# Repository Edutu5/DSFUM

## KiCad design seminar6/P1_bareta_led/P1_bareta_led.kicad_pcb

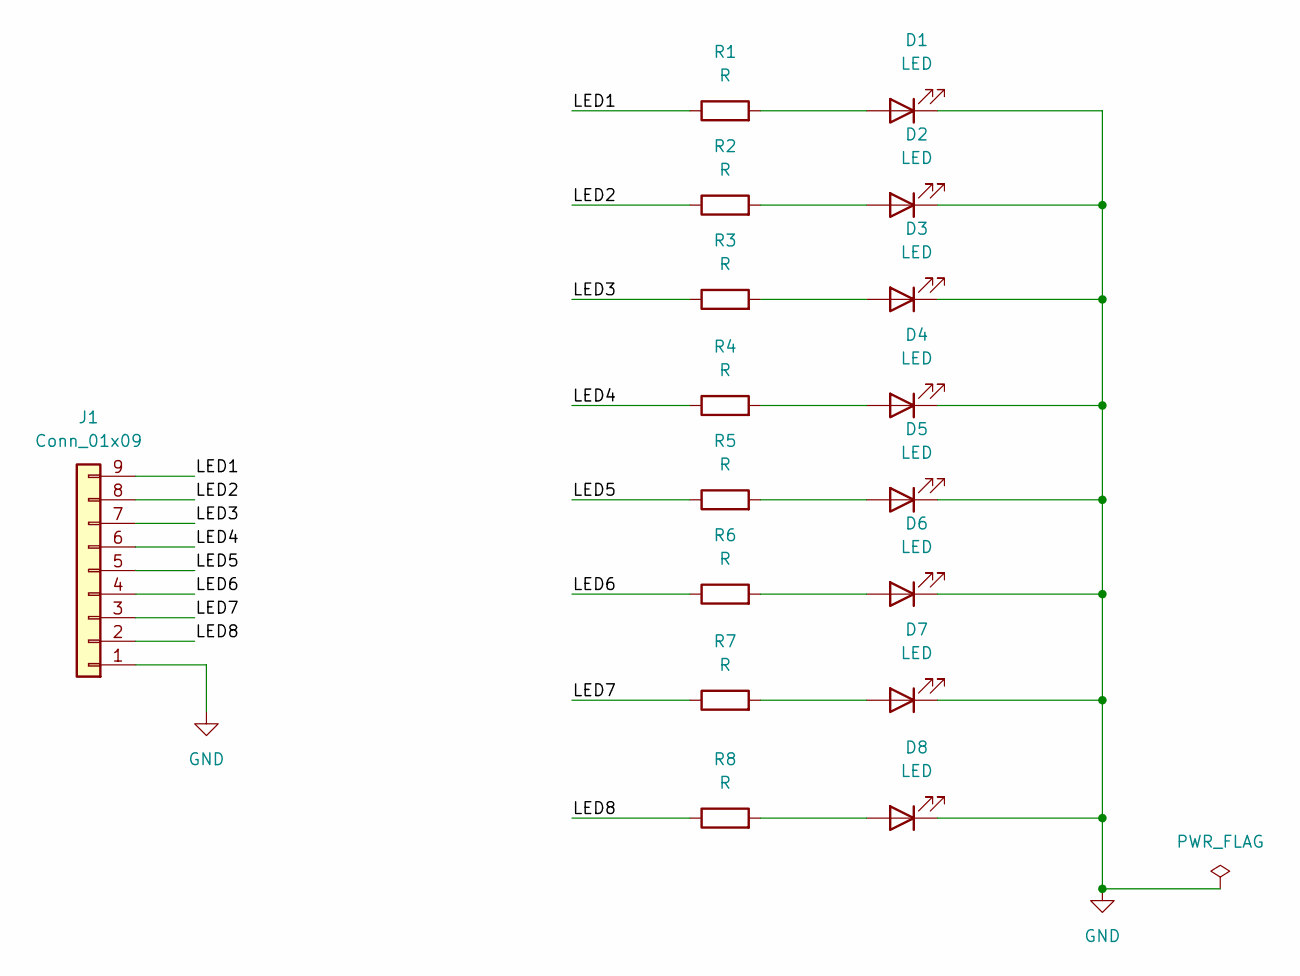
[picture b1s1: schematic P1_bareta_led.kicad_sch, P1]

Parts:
D1, D2, D3, D4, D5, D6, D7, D8: LED; LED_D5.0mm
J1: Conn_01x09
R1, R2, R3, R4, R5, R6, R7, R8: R; R_Axial_DIN0207_L6.3mm_D2.5mm_P10.16mm_Horizontal

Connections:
/LED1: J1.9, R1.1
/LED2: J1.8, R2.1
/LED3: J1.7, R3.1
/LED4: J1.6, R4.1
/LED5: J1.5, R5.1
/LED6: J1.4, R6.1
/LED7: J1.3, R7.1
/LED8: J1.2, R8.1
GND: D1.1 (K), D2.1 (K), D3.1 (K), D4.1 (K), D5.1 (K), D6.1 (K), D7.1 (K), D8.1 (K), J1.1
unnamed: D1.2 (A), R1.2
unnamed: D2.2 (A), R2.2
unnamed: D3.2 (A), R3.2
unnamed: D4.2 (A), R4.2
unnamed: D5.2 (A), R5.2
unnamed: D6.2 (A), R6.2
unnamed: D7.2 (A), R7.2
unnamed: D8.2 (A), R8.2

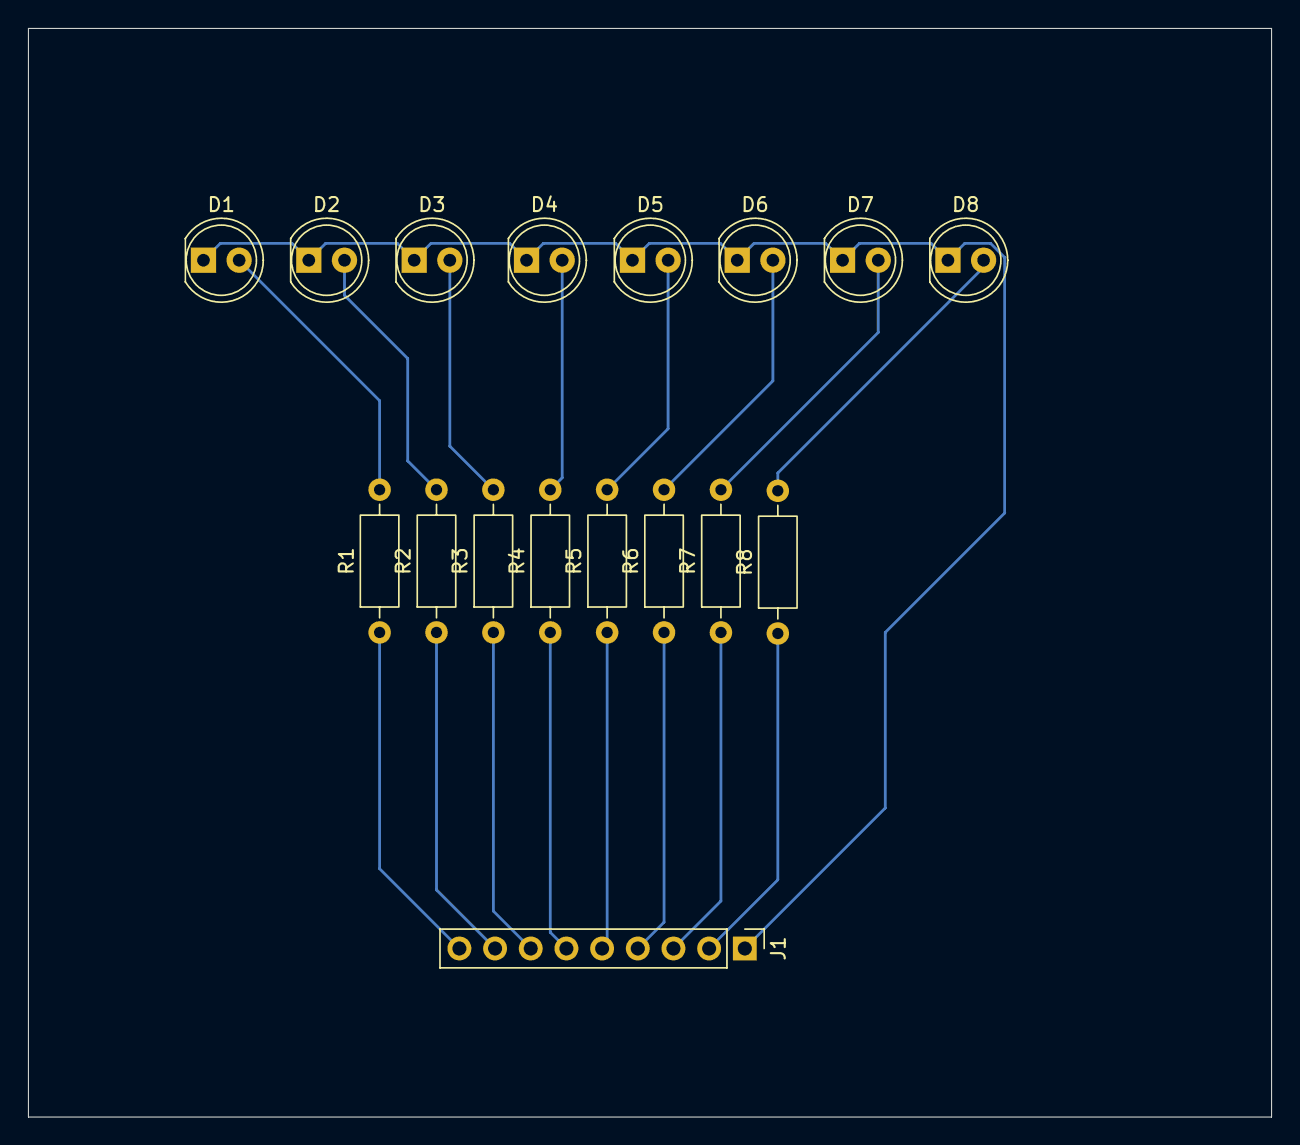
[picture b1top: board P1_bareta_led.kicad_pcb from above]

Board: 2 copper layers, 88.5 x 77.5 mm, 17 parts (0 on the bottom side), 17 nets.
